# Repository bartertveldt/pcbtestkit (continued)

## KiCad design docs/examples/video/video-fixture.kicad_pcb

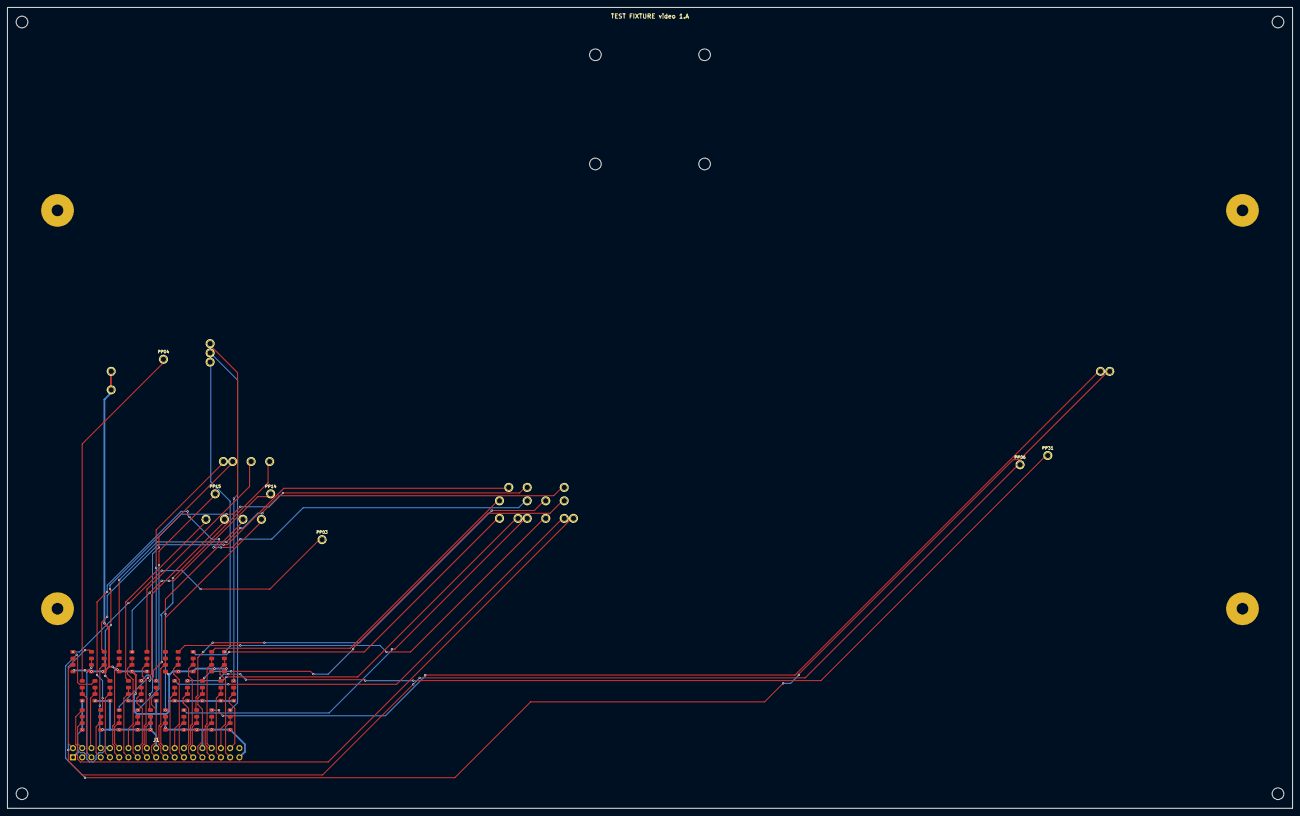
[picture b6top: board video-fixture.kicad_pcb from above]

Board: 2 copper layers, 353.0 x 220.0 mm, 113 parts (0 on the bottom side), 65 nets.

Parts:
H1, H2, H3, H4: M3 standoff; MountingHole_3.2mm
J1: TEST_IO; PinHeader_2x19_P2.54mm_Vertical
K1: TOGGLE CLAMP; ToggleClamp
N1: NEST; Nest
NK1, NK2, NK3, NK4: CLAMP M3; ClampScrew_M3
NP1, NP2, NP3, NP4: STANDOFF M3; NestPost_M3
P1, P2: GND; Pogo_P75_receptacle
P3: +3.3V; Pogo_P75_receptacle
P4: +5F; Pogo_P75_receptacle
P5: +5V; Pogo_P75_receptacle
P6: VAA; Pogo_P75_receptacle
P7: BLANK-; Pogo_P75_receptacle
P8: EA1; Pogo_P75_receptacle
P9: EA2; Pogo_P75_receptacle
P10: EA3; Pogo_P75_receptacle
P11: EA4; Pogo_P75_receptacle
P12: EA5; Pogo_P75_receptacle
P13: EA6; Pogo_P75_receptacle
P14: EA7; Pogo_P75_receptacle
P15: EA9; Pogo_P75_receptacle
P16: EA10; Pogo_P75_receptacle
P17: EA11; Pogo_P75_receptacle
P18: EA12; Pogo_P75_receptacle
P19: EA13; Pogo_P75_receptacle
P20: EA14; Pogo_P75_receptacle
P21: EA15; Pogo_P75_receptacle
P22: EQ0; Pogo_P75_receptacle
P23: EQ1; Pogo_P75_receptacle
P24: EQ2; Pogo_P75_receptacle
P25: EQ3; Pogo_P75_receptacle
P26: EQ4; Pogo_P75_receptacle
P27: EQ5; Pogo_P75_receptacle
P28: EQ6; Pogo_P75_receptacle
P29: EQ7; Pogo_P75_receptacle
P30: CLKCDA; Pogo_P75_receptacle
P31: CSYNCIN-; Pogo_P75_receptacle
P32: DQ8; Pogo_P75_receptacle
P33: DQ9; Pogo_P75_receptacle
P34: DQ10; Pogo_P75_receptacle
R1: 1.8k; R_0805_2012Metric
R2, R4, R6, R8: 10k; R_0805_2012Metric
R3, R5, R7: 8.2k; R_0805_2012Metric
R9, R11, R13, R15, R17, R19, R21, R23, R25, R27, R29, R31, R33, R35, R37, R39, R41, R43, R45, R47, R49, R51, R53, R55, R57, R59, R61, R63: 82k; R_0805_2012Metric
R10, R12, R14, R16, R18, R20, R22, R24, R26, R28, R30, R32, R34, R36, R38, R40, R42, R44, R46, R48, R50, R52, R54, R56, R58, R60, R62, R64: 100k; R_0805_2012Metric

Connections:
CH01: J1.2 (CH01), R1.1, R2.2
CH02: J1.3 (CH02), R3.1, R4.2
CH03: J1.4 (CH03), R5.1, R6.2
CH04: J1.5 (CH04), R7.1, R8.2
CH05: J1.6 (CH05), R9.1, R10.2
CH06: J1.7 (CH06), R11.1, R12.2
CH07: J1.8 (CH07), R13.1, R14.2
CH08: J1.9 (CH08), R15.1, R16.2
CH09: J1.11 (CH09), R17.1, R18.2
CH10: J1.12 (CH10), R19.1, R20.2
CH11: J1.13 (CH11), R21.1, R22.2
CH12: J1.14 (CH12), R23.1, R24.2
CH13: J1.15 (CH13), R25.1, R26.2
CH14: J1.16 (CH14), R27.1, R28.2
CH15: J1.17 (CH15), R29.1, R30.2
CH16: J1.18 (CH16), R31.1, R32.2
CH17: J1.19 (CH17), R33.1, R34.2
CH18: J1.21 (CH18), R35.1, R36.2
CH19: J1.22 (CH19), R37.1, R38.2
CH20: J1.23 (CH20), R39.1, R40.2
CH21: J1.24 (CH21), R41.1, R42.2
CH22: J1.25 (CH22), R43.1, R44.2
CH23: J1.26 (CH23), R45.1, R46.2
CH24: J1.27 (CH24), R47.1, R48.2
CH25: J1.28 (CH25), R49.1, R50.2
CH26: J1.29 (CH26), R51.1, R52.2
CH27: J1.31 (CH27), R53.1, R54.2
CH28: J1.32 (CH28), R55.1, R56.2
CH29: J1.33 (CH29), R57.1, R58.2
CH30: J1.34 (CH30), R59.1, R60.2
CH31: J1.35 (CH31), R61.1, R62.2
CH32: J1.36 (CH32), R63.1, R64.2
GND: J1.1 (GND), J1.10 (GND), J1.20 (GND), J1.30 (GND), J1.37 (GND), P1.1, P2.1, R2.1, R4.1, R6.1, R8.1, R10.1, R12.1, R14.1, R16.1, R18.1, R20.1, R22.1, R24.1, R26.1, R28.1, R30.1, R32.1, R34.1, R36.1, R38.1, R40.1, R42.1, R44.1, R46.1, R48.1, R50.1, R52.1, R54.1, R56.1, R58.1, R60.1, R62.1, R64.1
TP_+3.3V: P3.1, R1.2
TP_+5F: P4.1, R3.2
TP_+5V: P5.1, R5.2
TP_BLANK-: P7.1, R9.2
TP_CLKCDA: P30.1, R55.2
TP_CSYNCIN-: P31.1, R57.2
TP_DQ8: P32.1, R59.2
TP_DQ9: P33.1, R61.2
TP_DQ10: P34.1, R63.2
TP_EA1: P8.1, R11.2
TP_EA2: P9.1, R13.2
TP_EA3: P10.1, R15.2
TP_EA4: P11.1, R17.2
TP_EA5: P12.1, R19.2
TP_EA6: P13.1, R21.2
TP_EA7: P14.1, R23.2
TP_EA9: P15.1, R25.2
TP_EA10: P16.1, R27.2
TP_EA11: P17.1, R29.2
TP_EA12: P18.1, R31.2
TP_EA13: P19.1, R33.2
TP_EA14: P20.1, R35.2
TP_EA15: P21.1, R37.2
TP_EQ0: P22.1, R39.2
TP_EQ1: P23.1, R41.2
TP_EQ2: P24.1, R43.2
TP_EQ3: P25.1, R45.2
TP_EQ4: P26.1, R47.2
TP_EQ5: P27.1, R49.2
TP_EQ6: P28.1, R51.2
TP_EQ7: P29.1, R53.2
TP_VAA: P6.1, R7.2

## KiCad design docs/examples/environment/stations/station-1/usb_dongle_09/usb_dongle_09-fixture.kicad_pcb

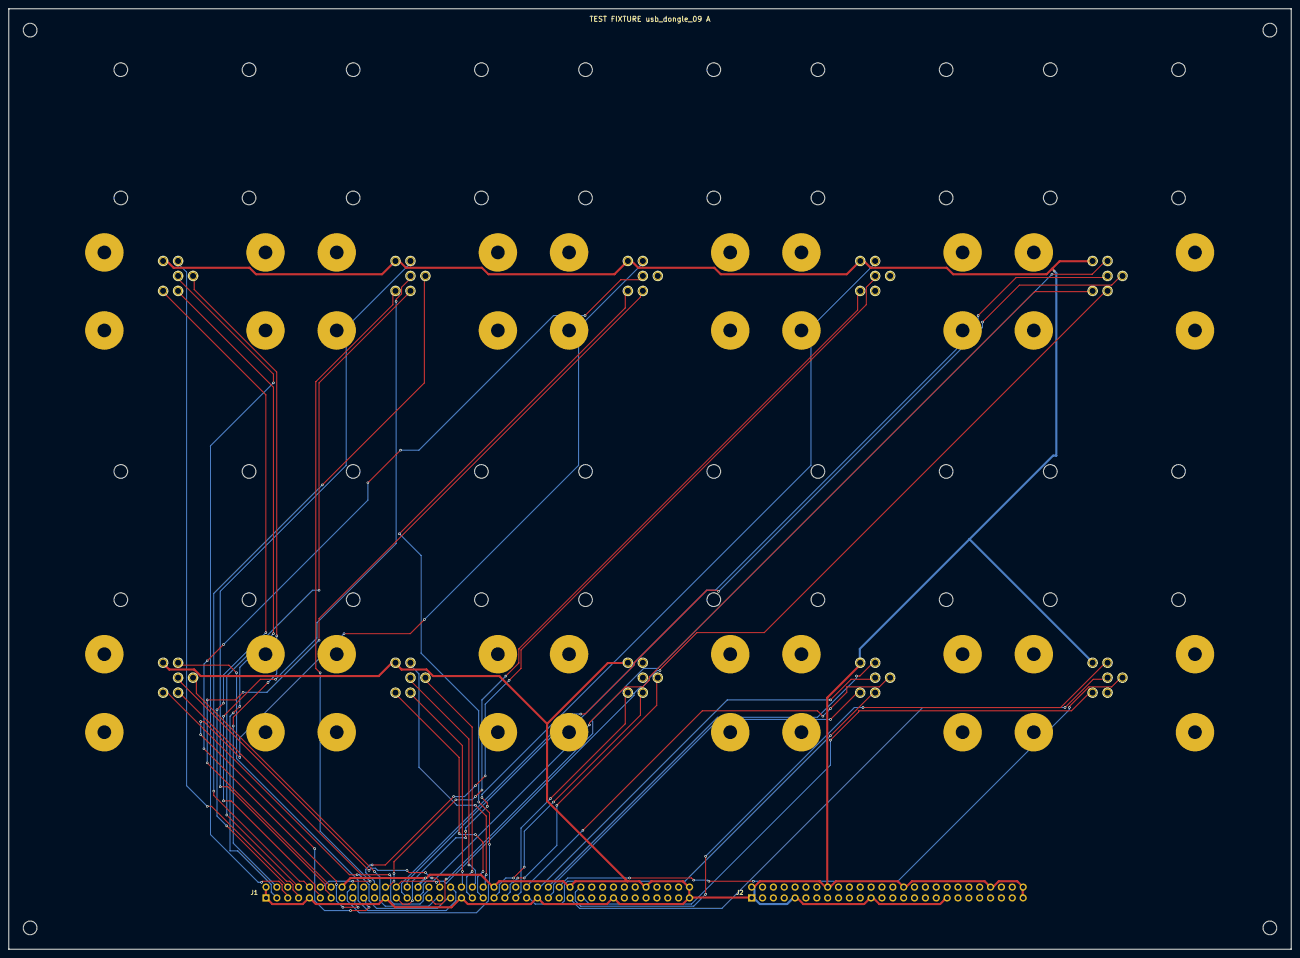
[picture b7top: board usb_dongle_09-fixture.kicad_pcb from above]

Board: 2 copper layers, 300.0 x 220.0 mm, 166 parts (0 on the bottom side), 51 nets.

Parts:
H1, H2, H3, H4: M3; MountingHole_3.2mm
J1: J1; PinHeader_2x40_P2.54mm_Vertical
J2: J2; PinHeader_2x26_P2.54mm_Vertical
K1, K2, K3, K4, K5, K6, K7, K8, K9, K10: TOGGLE CLAMP; ToggleClamp
N1, N2, N3, N4, N5, N6, N7, N8, N9, N10: NEST; Nest
NK1, NK2, NK3, NK4, NK5, NK6, NK7, NK8, NK9, NK10, NK11, NK12, NK13, NK14, NK15, NK16, NK17, NK18, NK19, NK20, NK21, NK22, NK23, NK24, NK25, NK26, NK27, NK28, NK29, NK30, NK31, NK32, NK33, NK34, NK35, NK36, NK37, NK38, NK39, NK40: CLAMP M3; ClampScrew_M3
NP1, NP2, NP3, NP4, NP5, NP6, NP7, NP8, NP9, NP10, NP11, NP12, NP13, NP14, NP15, NP16, NP17, NP18, NP19, NP20, NP21, NP22, NP23, NP24, NP25, NP26, NP27, NP28, NP29, NP30, NP31, NP32, NP33, NP34, NP35, NP36, NP37, NP38, NP39, NP40: STANDOFF M3; NestPost_M3
P1, P7, P13, P19, P25, P31, P37, P43, P49, P55: GND; Pogo_P75_receptacle
P2, P8, P14, P20, P26, P32, P38, P44, P50, P56: +3V3; Pogo_P75_receptacle
P3, P9, P15, P21, P27, P33, P39, P45, P51, P57: VBUS; Pogo_P75_receptacle
P4, P10, P16, P22, P28, P34, P40, P46, P52, P58: NRST; Pogo_P75_receptacle
P5, P11, P17, P23, P29, P35, P41, P47, P53, P59: SWCLK; Pogo_P75_receptacle
P6, P12, P18, P24, P30, P36, P42, P48, P54, P60: USB_D+; Pogo_P75_receptacle

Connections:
GND: J1.1 (GND), J1.2 (GND), J1.9 (GND), J1.16 (GND), J1.23 (GND), J1.30 (GND), J1.37 (GND), J1.44 (GND), J1.51 (GND), J1.58 (GND), J1.65 (GND), J1.72 (GND), J1.79 (GND), J1.80 (GND), J2.1 (GND), J2.2 (GND), J2.9 (GND), J2.16 (GND), J2.23 (GND), J2.30 (GND), J2.37 (GND), J2.46 (GND), J2.51 (GND), J2.52 (GND), P1.1, P7.1, P13.1, P19.1, P25.1, P31.1, P37.1, P43.1, P49.1, P55.1
S1_TP_+3V3: J1.3 (AIN1), P2.1
S1_TP_NRST: J1.5 (AIN3), P4.1
S1_TP_SWCLK: J1.6 (AIN4), P5.1
S1_TP_USB_D+: J1.7 (AIN5), P6.1
S1_TP_VBUS: J1.4 (AIN2), P3.1
S2_TP_+3V3: J1.8 (AIN6), P8.1
S2_TP_NRST: J1.11 (AIN8), P10.1
S2_TP_SWCLK: J1.12 (AIN9), P11.1
S2_TP_USB_D+: J1.13 (AIN10), P12.1
S2_TP_VBUS: J1.10 (AIN7), P9.1
S3_TP_+3V3: J1.14 (AIN11), P14.1
S3_TP_NRST: J1.17 (AIN13), P16.1
S3_TP_SWCLK: J1.18 (AIN14), P17.1
S3_TP_USB_D+: J1.19 (AIN15), P18.1
S3_TP_VBUS: J1.15 (AIN12), P15.1
S4_TP_+3V3: J1.20 (AIN16), P20.1
S4_TP_NRST: J1.22 (AIN18), P22.1
S4_TP_SWCLK: J1.24 (AIN19), P23.1
S4_TP_USB_D+: J1.25 (AIN20), P24.1
S4_TP_VBUS: J1.21 (AIN17), P21.1
S5_TP_+3V3: J1.26 (AIN21), P26.1
S5_TP_NRST: J1.28 (AIN23), P28.1
S5_TP_SWCLK: J1.29 (AIN24), P29.1
S5_TP_USB_D+: J1.31 (AIN25), P30.1
S5_TP_VBUS: J1.27 (AIN22), P27.1
S6_TP_+3V3: J1.32 (AIN26), P32.1
S6_TP_NRST: J1.34 (AIN28), P34.1
S6_TP_SWCLK: J1.35 (AIN29), P35.1
S6_TP_USB_D+: J1.36 (AIN30), P36.1
S6_TP_VBUS: J1.33 (AIN27), P33.1
S7_TP_+3V3: J1.38 (AIN31), P38.1
S7_TP_NRST: J1.40 (AIN33), P40.1
S7_TP_SWCLK: J1.41 (AIN34), P41.1
S7_TP_USB_D+: J1.42 (AIN35), P42.1
S7_TP_VBUS: J1.39 (AIN32), P39.1
S8_TP_+3V3: J1.43 (AIN36), P44.1
S8_TP_NRST: J1.46 (AIN38), P46.1
S8_TP_SWCLK: J1.47 (AIN39), P47.1
S8_TP_USB_D+: J1.48 (AIN40), P48.1
S8_TP_VBUS: J1.45 (AIN37), P45.1
S9_TP_+3V3: J1.49 (AIN41), P50.1
S9_TP_NRST: J1.52 (AIN43), P52.1
S9_TP_SWCLK: J1.53 (AIN44), P53.1
S9_TP_USB_D+: J1.54 (AIN45), P54.1
S9_TP_VBUS: J1.50 (AIN42), P51.1
S10_TP_+3V3: J1.55 (AIN46), P56.1
S10_TP_NRST: J1.57 (AIN48), P58.1
S10_TP_SWCLK: J1.59 (AIN49), P59.1
S10_TP_USB_D+: J1.60 (AIN50), P60.1
S10_TP_VBUS: J1.56 (AIN47), P57.1

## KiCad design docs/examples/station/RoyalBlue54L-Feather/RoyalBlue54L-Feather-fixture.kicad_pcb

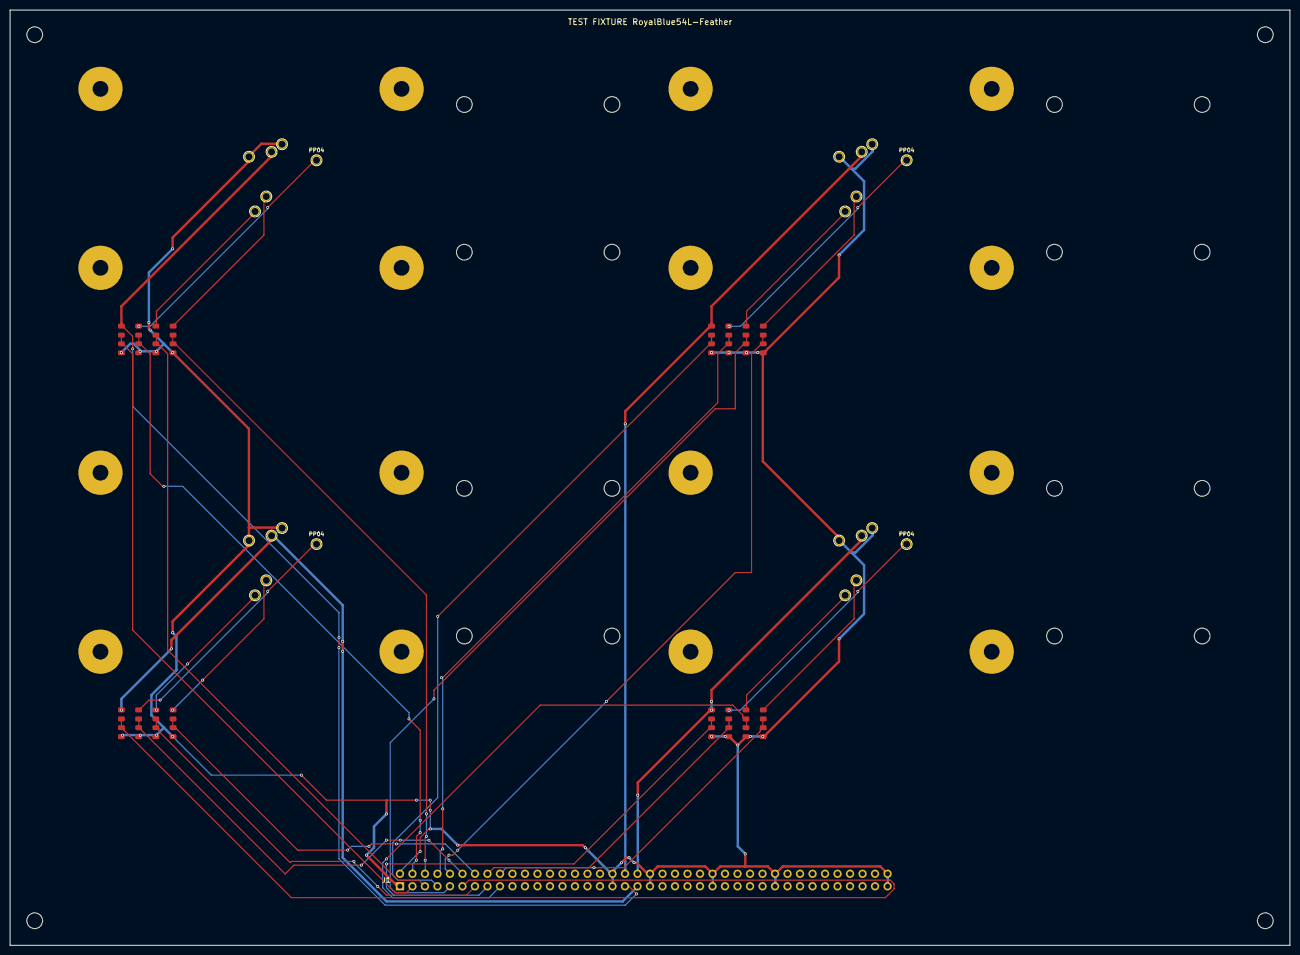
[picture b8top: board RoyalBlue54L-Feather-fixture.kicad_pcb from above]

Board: 2 copper layers, 260.0 x 190.0 mm, 101 parts (0 on the bottom side), 33 nets.

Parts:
H1, H2, H3, H4: M3; MountingHole_3.2mm
J1: J1; PinHeader_2x40_P2.54mm_Vertical
K1, K2, K3, K4: TOGGLE CLAMP; ToggleClamp
N1, N2, N3, N4: NEST; Nest
NK1, NK2, NK3, NK4, NK5, NK6, NK7, NK8, NK9, NK10, NK11, NK12, NK13, NK14, NK15, NK16: CLAMP M3; ClampScrew_M3
NP1, NP2, NP3, NP4, NP5, NP6, NP7, NP8, NP9, NP10, NP11, NP12, NP13, NP14, NP15, NP16: STANDOFF M3; NestPost_M3
P1, P7, P13, P19: USB.VBUS; Pogo_P75_receptacle
P2, P3, P8, P9, P14, P15, P20, P21: GND; Pogo_P75_receptacle
P4, P10, P16, P22: +BATT; Pogo_P75_receptacle
P5, P11, P17, P23: Net-(JP1-A); Pogo_P75_receptacle
P6, P12, P18, P24: VSYS; Pogo_P75_receptacle
R1, R3, R5, R7, R9, R11, R13, R15, R17, R19, R21, R23, R25, R27, R29, R31: 8.2k; R_0805_2012Metric
R2, R4, R6, R8, R10, R12, R14, R16, R18, R20, R22, R24, R26, R28, R30, R32: 10k; R_0805_2012Metric

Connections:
GND: J1.1 (GND), J1.2 (GND), J1.35 (GND), J1.36 (GND), J1.41 (GND), J1.42 (GND), J1.51 (GND), J1.52 (GND), J1.61 (GND), J1.62 (GND), J1.79 (GND), J1.80 (GND), P2.1, P3.1, P8.1, P9.1, P14.1, P15.1, P20.1, P21.1, R2.1, R4.1, R6.1, R8.1, R10.1, R12.1, R14.1, R16.1, R18.1, R20.1, R22.1, R24.1, R26.1, R28.1, R30.1, R32.1
S1_CH01: J1.3 (AIN1), R1.1, R2.2
S1_CH02: J1.4 (AIN2), R3.1, R4.2
S1_CH03: J1.5 (AIN3), R5.1, R6.2
S1_CH04: J1.6 (AIN4), R7.1, R8.2
S1_TP_+BATT: P4.1, R3.2
S1_TP_Net-_JP1-A: P5.1, R5.2
S1_TP_VSYS: P6.1, R7.2
S1_VIN: J1.37 (VOUT1), P1.1, R1.2
S2_CH01: J1.7 (AIN5), R9.1, R10.2
S2_CH02: J1.8 (AIN6), R11.1, R12.2
S2_CH03: J1.9 (AIN7), R13.1, R14.2
S2_CH04: J1.10 (AIN8), R15.1, R16.2
S2_TP_+BATT: P10.1, R11.2
S2_TP_Net-_JP1-A: P11.1, R13.2
S2_TP_VSYS: P12.1, R15.2
S2_VIN: J1.38 (VOUT2), P7.1, R9.2
S3_CH01: J1.11 (AIN9), R17.1, R18.2
S3_CH02: J1.12 (AIN10), R19.1, R20.2
S3_CH03: J1.13 (AIN11), R21.1, R22.2
S3_CH04: J1.14 (AIN12), R23.1, R24.2
S3_TP_+BATT: P16.1, R19.2
S3_TP_Net-_JP1-A: P17.1, R21.2
S3_TP_VSYS: P18.1, R23.2
S3_VIN: J1.39 (VOUT3), P13.1, R17.2
S4_CH01: J1.15 (AIN13), R25.1, R26.2
S4_CH02: J1.16 (AIN14), R27.1, R28.2
S4_CH03: J1.17 (AIN15), R29.1, R30.2
S4_CH04: J1.18 (AIN16), R31.1, R32.2
S4_TP_+BATT: P22.1, R27.2
S4_TP_Net-_JP1-A: P23.1, R29.2
S4_TP_VSYS: P24.1, R31.2
S4_VIN: J1.40 (VOUT4), P19.1, R25.2
